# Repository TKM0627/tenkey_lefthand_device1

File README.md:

# 4x4 Tenkey - Raspberry Pi Pico (RP2040)

Based on tenkey.kicad_pcb: rows GP1, GP2, GP4, GP5; columns GP6, GP7, GP9, GP10; diode direction COL2ROW.

## Build
1. Set up QMK environment: https://docs.qmk.fm/newbs_getting_started
2. Copy `keyboards/otto_tenkey` into `qmk_firmware/keyboards/`.
3. Run: `qmk compile -kb otto_tenkey -km default`
4. Find the generated `.uf2` in `qmk_firmware/`.
5. Hold BOOTSEL while connecting Pico over USB. Release BOOTSEL, then copy `.uf2` into RPI-RP2 drive.

These are source files, NOT a precompiled firmware UF2. Verify solder joints and absence of supply shorts before attaching USB.

Note: The VID/PID are placeholders for personal development; replace them with appropriate assigned identifiers before distribution.

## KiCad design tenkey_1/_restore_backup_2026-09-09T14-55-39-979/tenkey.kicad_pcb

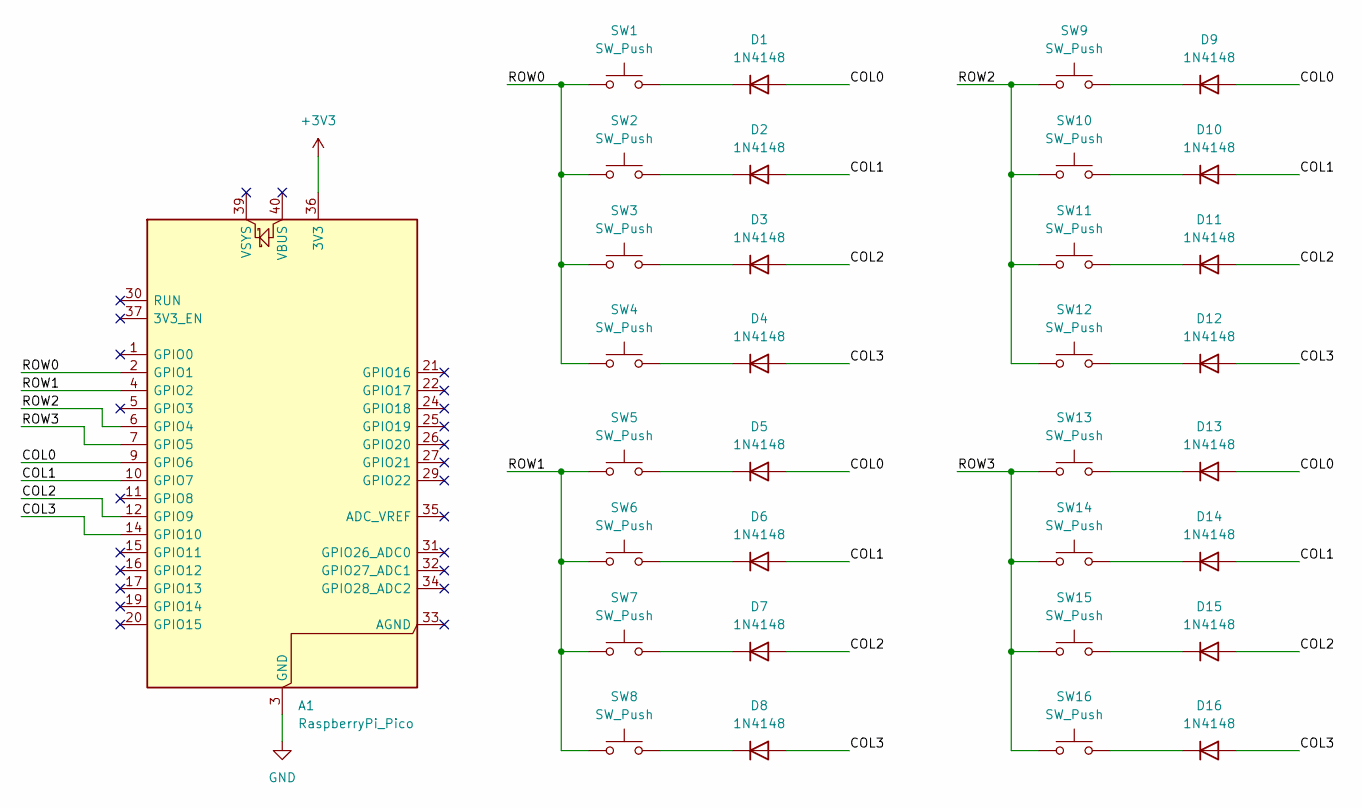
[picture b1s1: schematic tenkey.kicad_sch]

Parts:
A1: RaspberryPi_Pico; RaspberryPi_Pico_Common_THT
D1, D2, D3, D4, D5, D6, D7, D8, D9, D10, D11, D12, D13, D14, D15, D16: 1N4148; D_DO-35_SOD27_P7.62mm_Horizontal
SW1, SW2, SW3, SW4, SW5, SW6, SW7, SW8, SW9, SW10, SW11, SW12, SW13, SW14, SW15, SW16: SW_Push; SW_Hotswap_Kailh_MX_1.00u

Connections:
+3V3: A1.36 (3V3)
/COL0: A1.9 (GPIO6), D1.2 (A), D5.2 (A), D9.2 (A), D13.2 (A)
/COL1: A1.10 (GPIO7), D2.2 (A), D6.2 (A), D10.2 (A), D14.2 (A)
/COL2: A1.12 (GPIO9), D3.2 (A), D7.2 (A), D11.2 (A), D15.2 (A)
/COL3: A1.14 (GPIO10), D4.2 (A), D8.2 (A), D12.2 (A), D16.2 (A)
/ROW0: A1.2 (GPIO1), SW1.1, SW2.1, SW3.1, SW4.1
/ROW1: A1.4 (GPIO2), SW5.1, SW6.1, SW7.1, SW8.1
/ROW2: A1.6 (GPIO4), SW9.1, SW10.1, SW11.1, SW12.1
/ROW3: A1.7 (GPIO5), SW13.1, SW14.1, SW15.1, SW16.1
GND: A1.3 (GND), A1.8 (GND), A1.13 (GND), A1.18 (GND), A1.23 (GND), A1.28 (GND), A1.38 (GND)
unnamed: D1.1 (K), SW1.2
unnamed: D2.1 (K), SW2.2
unnamed: D3.1 (K), SW3.2
unnamed: D4.1 (K), SW4.2
unnamed: D5.1 (K), SW5.2
unnamed: D6.1 (K), SW6.2
unnamed: D7.1 (K), SW7.2
unnamed: D8.1 (K), SW8.2
unnamed: D9.1 (K), SW9.2
unnamed: D10.1 (K), SW10.2
unnamed: D11.1 (K), SW11.2
unnamed: D12.1 (K), SW12.2
unnamed: D13.1 (K), SW13.2
unnamed: D14.1 (K), SW14.2
unnamed: D15.1 (K), SW15.2
unnamed: D16.1 (K), SW16.2

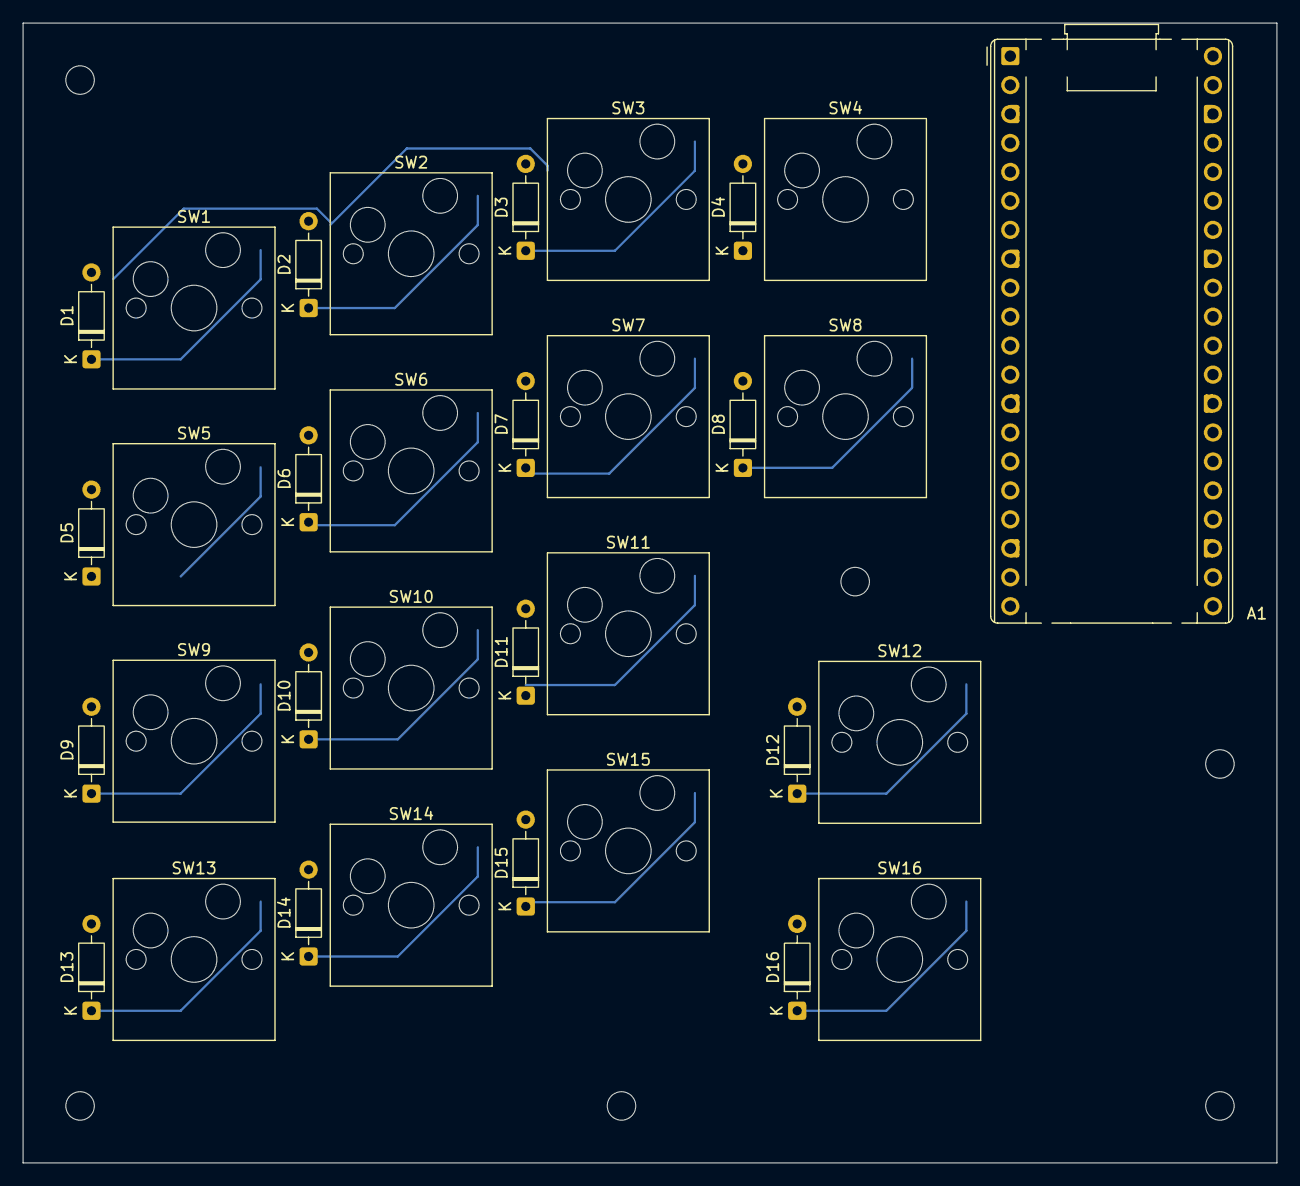
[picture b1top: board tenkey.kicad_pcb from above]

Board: 2 copper layers, 110.0 x 100.0 mm, 33 parts (0 on the bottom side), 25 nets.
